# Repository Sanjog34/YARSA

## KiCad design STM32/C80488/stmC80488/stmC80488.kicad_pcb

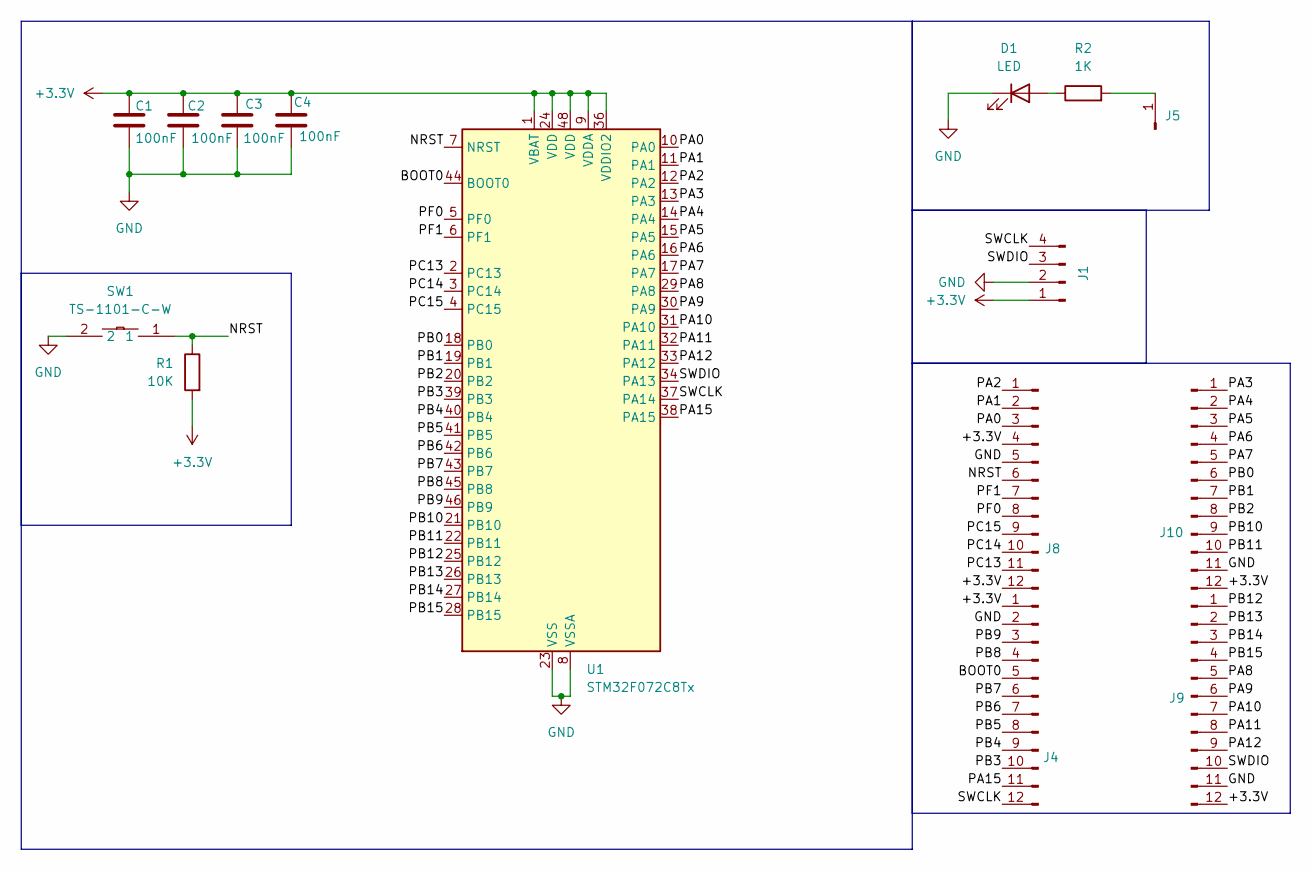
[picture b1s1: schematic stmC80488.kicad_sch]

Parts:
C1, C2, C3, C4: 100nF; C_0805_2012Metric
D1: LED; LED_0603_1608Metric
J1: Conn_01x04_Pin; PinHeader_1x04_P2.54mm_Vertical
J4, J8, J9, J10: Conn_01x12_Pin; PinHeader_1x12_P2.54mm_Vertical
J5: Conn_01x01_Pin; PinHeader_1x01_P2.54mm_Vertical
R1: 10K; R_0603_1608Metric
R2: 1K; R_0603_1608Metric
SW1: TS-1101-C-W; SW-SMD_L6.0-W3.3-LS8.0; LCSC Part C318938
U1: STM32F072C8Tx; LQFP-48_7x7mm_P0.5mm

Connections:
+3.3V: C1.1, C2.1, C3.1, C4.1, J1.1, J4.1, J8.4, J8.12, J9.12, J10.12, R1.2, U1.1 (VBAT), U1.9 (VDDA), U1.24 (VDD), U1.36 (VDDIO2), U1.48 (VDD)
/BOOT0: J4.5, U1.44 (BOOT0)
/NRST: J8.6, R1.1, SW1.1, U1.7 (NRST)
/PA0: J8.3, U1.10 (PA0)
/PA1: J8.2, U1.11 (PA1)
/PA2: J8.1, U1.12 (PA2)
/PA3: J10.1, U1.13 (PA3)
/PA4: J10.2, U1.14 (PA4)
/PA5: J10.3, U1.15 (PA5)
/PA6: J10.4, U1.16 (PA6)
/PA7: J10.5, U1.17 (PA7)
/PA8: J9.5, U1.29 (PA8)
/PA9: J9.6, U1.30 (PA9)
/PA10: J9.7, U1.31 (PA10)
/PA11: J9.8, U1.32 (PA11)
/PA12: J9.9, U1.33 (PA12)
/PA15: J4.11, U1.38 (PA15)
/PB0: J10.6, U1.18 (PB0)
/PB1: J10.7, U1.19 (PB1)
/PB2: J10.8, U1.20 (PB2)
/PB3: J4.10, U1.39 (PB3)
/PB4: J4.9, U1.40 (PB4)
/PB5: J4.8, U1.41 (PB5)
/PB6: J4.7, U1.42 (PB6)
/PB7: J4.6, U1.43 (PB7)
/PB8: J4.4, U1.45 (PB8)
/PB9: J4.3, U1.46 (PB9)
/PB10: J10.9, U1.21 (PB10)
/PB11: J10.10, U1.22 (PB11)
/PB12: J9.1, U1.25 (PB12)
/PB13: J9.2, U1.26 (PB13)
/PB14: J9.3, U1.27 (PB14)
/PB15: J9.4, U1.28 (PB15)
/PC13: J8.11, U1.2 (PC13)
/PC14: J8.10, U1.3 (PC14)
/PC15: J8.9, U1.4 (PC15)
/PF0: J8.8, U1.5 (PF0)
/PF1: J8.7, U1.6 (PF1)
/SWCLK: J1.4, J4.12, U1.37 (PA14)
/SWDIO: J1.3, J9.10, U1.34 (PA13)
GND: C1.2, C2.2, C3.2, C4.2, D1.1 (K), J1.2, J4.2, J8.5, J9.11, J10.11, SW1.2, U1.8 (VSSA), U1.23 (VSS), U1.35 (VSS), U1.47 (VSS)
unnamed: D1.2 (A), R2.1
unnamed: J5.1, R2.2

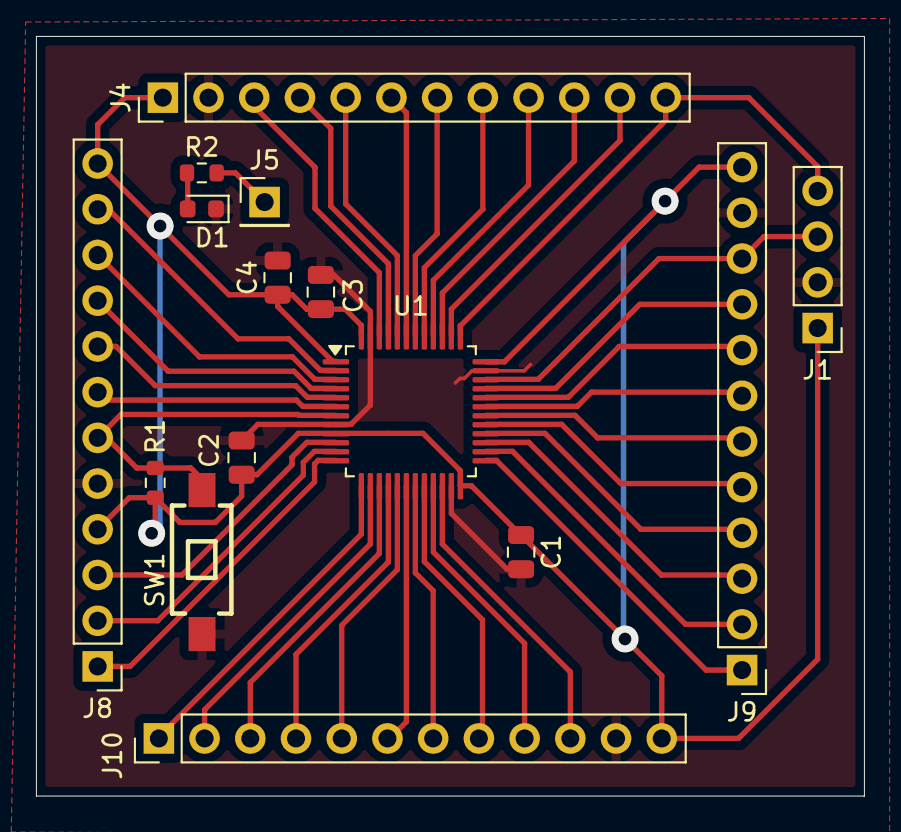
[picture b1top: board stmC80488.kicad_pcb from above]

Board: 2 copper layers, 46.0 x 42.2 mm, 15 parts (0 on the bottom side), 43 nets.

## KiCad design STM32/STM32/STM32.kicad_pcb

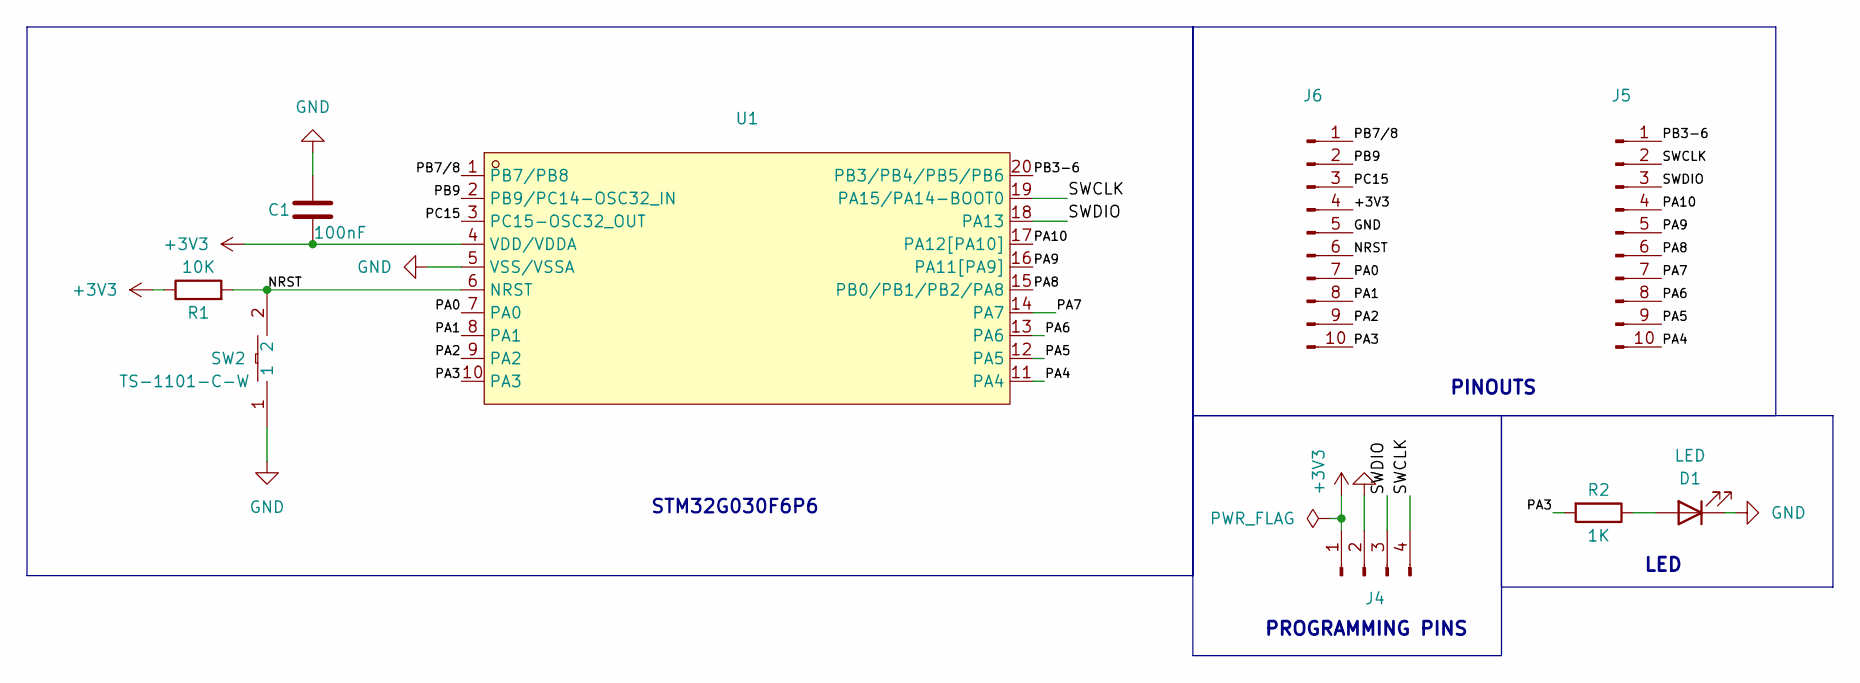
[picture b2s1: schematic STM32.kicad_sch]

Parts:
C1: 100nF; C_0805_2012Metric
D1: LED; LED_0603_1608Metric
J4: Conn_01x04_Pin; PinHeader_1x04_P2.54mm_Vertical
J5, J6: Conn_01x10_Pin; PinHeader_1x10_P2.54mm_Vertical
R1: 10K; R_0603_1608Metric
R2: 1K; R_0603_1608Metric
SW2: TS-1101-C-W; SW-SMD_L6.0-W3.3-LS8.0; LCSC Part C318938
U1: STM32G030F6P6; TSSOP-20_L6.5-W4.4-P0.65-LS6.4-BL; LCSC Part C724040

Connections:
+3V3: C1.2, J4.1, J6.4, R1.1, U1.4 (VDD/VDDA)
/NRST: J6.6, R1.2, SW2.2, U1.6 (NRST)
/PA0: J6.7, U1.7 (PA0)
/PA1: J6.8, U1.8 (PA1)
/PA2: J6.9, U1.9 (PA2)
/PA3: J6.10, R2.2, U1.10 (PA3)
/PA4: J5.10, U1.11 (PA4)
/PA5: J5.9, U1.12 (PA5)
/PA6: J5.8, U1.13 (PA6)
/PA7: J5.7, U1.14 (PA7)
/PA8: J5.6, U1.15 (PB0/PB1/PB2/PA8)
/PA9: J5.5, U1.16 (PA11[PA9])
/PA10: J5.4, U1.17 (PA12[PA10])
/PB3-6: J5.1, U1.20 (PB3/PB4/PB5/PB6)
/PB7/8: J6.1, U1.1 (PB7/PB8)
/PB9: J6.2, U1.2 (PB9/PC14-OSC32_IN)
/PC15: J6.3, U1.3 (PC15-OSC32_OUT)
/SWCLK: J4.4, J5.2, U1.19 (PA15/PA14-BOOT0)
/SWDIO: J4.3, J5.3, U1.18 (PA13)
GND: C1.1, D1.1 (K), J4.2, J6.5, SW2.1, U1.5 (VSS/VSSA)
unnamed: D1.2 (A), R2.1

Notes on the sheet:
PROGRAMMING PINS
PINOUTS
LED
STM32G030F6P6

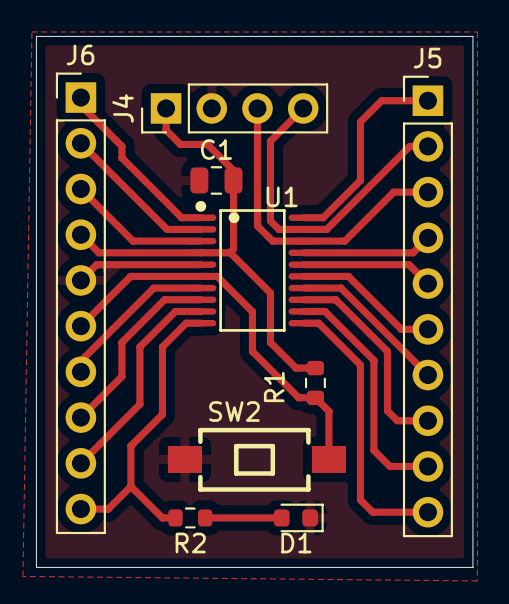
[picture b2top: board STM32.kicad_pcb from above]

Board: 2 copper layers, 24.2 x 29.5 mm, 9 parts (0 on the bottom side), 21 nets.

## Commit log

2024-09-18 backups
2024-09-18 backup
